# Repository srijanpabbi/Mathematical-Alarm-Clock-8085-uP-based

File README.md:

# Mathematical-Alarm-Clock
#[Find PDF in git repo(Brief Document)]
This device aims to make turning off an alarm a slightly more involving task, forcing the user to focus on the device for some time hence breaking the sleep. It will keep track of time using a RTC and will sound an alarm on the preset time and throw a randomly generated integer based mathematical problem at the user(+,-,/,*), the alarm will stop ringing as soon as the user enters the correct answer to the question. This projects will incorporate a display, a keypad, alarm sounding system(buzzer), and a RTC.

## NETAJI SUBHAS INSTITUTE OFTECHNOLOGY

## DIVISION OFELECTRONICS AND COMMUNICATIONENGINEERING

### EC316 MICROPROCESSORLABPROJECTREPORT

# Mathematical Alarm Clock

## ANINTEL8085 MICROPROCESSOR BASED PROJECT

### Submitted by

### Prabhat Gupta (124EC15)

### Srijan Pabbi (173EC15)

### Submitted to

### Prof. Dhananjay V. Gadre

### May, 2018

## Contents

- 1 Abstract
- 2 Background And Motivation
- 3 Justification
- 4 Block Diagram
- 5 Technical Details
   - 5.1 Hardware
      - 5.1.1 Core Microprocessor (Intel 80C85)
      - 5.1.2 Peripherals And Addressing
      - 5.1.3 RTC(Real Time Clock)
      - 5.1.4 20x4 Character LCD
      - 5.1.5 Key-Pad
      - 5.1.6 Buzzer
   - 5.2 Software Implementation and Interesting Concepts
      - 5.2.1 Big Font and LCD Posting Techniques
      - 5.2.2 Key-Pad Scanning
      - 5.2.3 LFSR(Linear Feedback Shift Register) Implementation
      - 5.2.4 User Setup Inputs With Interrupts
      - 5.2.5 Arithmetic Random Problem Generation With Result Check
- 6 Supporting Materials
   - 6.1 Support Links and References
   - 6.2 Project Schematic And Boards
   - 6.3 Bill of Materials

## 1 Abstract

Everyone must have seen the ordinary alarm clocks that sound only when it is set to be alarmed.Why not
to make a normal alarm period an interesting task. It’s time to get rid of the conventional alarm clocks.
Here what comes the mathematical alarm clock. The mathematical alarm clock is a device that modifies
a conventional alarm clock to a more advanced version that not only alarms but it also makes sure that
the user gets out of sleep for solving some mathematical problems.This device aims to make turning on an
alarm a slightly more involving task. It keeps the trackof time and displays it on the lcd. It does so by using
an RTC (parallel data bus). The Alarm can be set using a keypad. At the time of alarm, a buzzer sounds. The
buzzing of the alarm continues as long as the user would not give the correct answers of certain number of
mathematical problems. At the alarm preset time, the device throws a randomly generated integer based
mathematical problem based on simple arithmetic (+). The alarm stops only after the correct answer is
given by the user. The project incorporates a display (LCD 20x4),keypad, buzzer as an alarming system,
parallel bus RTC

## 2 Background And Motivation

EC-311/316 has provided us an opportunity to build this project under the able guidance of Prof Dhanan-
jay Gadre. The idea of this project is to learn and portray the skill of designing a microprocessor based
system and putting whatever we learn in this course into a useful application. This device aims to make
turning on an alarm a slightly more involving task, forcing the user to focus on the device for some time
hence successfully breaking the sleep as compared to normal alarm clocks. Making this project will involve
almost all the steps required for making a embedded system product namely; planning, designing, getting
the pcb fabricated, coding, and a making an enclosure for the final display, and most importantly docu-
menting throughout the process of making it, which will give us experience on how to design a embedded
product from zero to finish.

## 3 Justification

Mathematical Alarm Clock involves the use of a RTC(Real Time Clock) for time keeping, 20x4 character
LCD for display of time and the generated math questions, and a user input keypad, these devices cannot
be used with simple digital logic devices to perform the job we want out of this project. This project must
be able to display time and, perform background mathematical calculations , accept and compare user
inputs to the answers of the questions which it generated randomly. The need to do all this for successful
working of the project the use of a microprocessor which is fairly fast and can perform slightly complex
mathematical calculations is justified.

## 4 Block Diagram

```
Figure 1: Block Diagram of Mathematical Alarm Clock
```

## 5 Technical Details

##### „„„„„„„„„„„„„„„„„„„„„„„„„„„„

### 5.1 Hardware

#### 5.1.1 Core Microprocessor (Intel 80C85)

At the heart of this project is an Intel 80C85 microprocessor( _μ_ P) from OKI Semiconductors is a CMOS im-
plementation of the original TTL 8085 which has a quiescent current of as low as 10mA. The microprocessor
has a 64KB memory address space and 256 bytes of I/O space. In this case the 8085 is running at 3MHz
from the clock of a 6MHz crystal oscillator.

```
Figure 2: OKI 8085
```

#### 5.1.2 Peripherals And Addressing

This project employs a Atmel ROM 28C256, Intel 8155 PPI+RAM+Timer, Maxim DS12887 RTC, as periph-
erals for the microprocessor and hence they occupy some part of the 8085’s address space.

- Atmel ROM 28C256: Is a 32KB rom which is over kill for this project but was chosen due to its ready
    availability and most of the address space of the 8085 microprocessor is not in use.
    -The address space for the ROM ranges from 0000hto 0FFFh.
    -Chip Select(CS) for this IC is connected toA 15 of the _μ_ P
- Intel 8155: Is a IC specially developed to be used with the Intel 8085 _μ_ P. It has 256bytes of RAM, 3
    I/O ports 2 of 8bit and 1 of 6bit, with handshake capability using the former as I/O and the latter for
    handshaking, and a 8 bit timer with clock out.
    -The address space for the RAM ranges from 8000hto 80FFh.
    -The IO addresses for 8155CWR-00h, PORTA-01h, PORTB-02h, PORTC-03h
    -Chip Select(CS) for this IC is connected toA 15 of the _μ_ P
- RTC: This IC is a complete package of an RTC, battery, and crystal, along with a non-volatile RAM in
    the RTC. This chip implements the Intel Bus Protocol Internally and hence can be memory mapped.
    -The address space for the RTC ranges from 8100hto 8180h.
    -Chip Select(CS) for this IC is connected via a decoding logic as shown in Figure 7

#### 5.1.3 RTC(Real Time Clock)

The real time clock employed for this project DS12887A from Maxim Integrated is a parallel bus RTC with
data exchange via the Intel bus protocol implemented internally. This RTC comes in a 24 pin EDIP package
with internally implemented crystal oscillator and a battery. It can count time on both binary as well as
BCD format with one-time of the day alarm, and an added feature of daylight saving by keeping track
of the exact day,date,year,and century of the millennium. Alongside the basic time keeping features, it
can interrupt the processor about an alarm situation. It can also produce a square wave out of various
frequencies which can be used to drive an alarm sounding system.
The following is the schematic implementation of the RTC.

#### 5.1.4 20x4 Character LCD

The display used in our project is 20X4 LCD display. It is said so as it has 4 rows with 20 characters each.
It uses HD44780 driver. The customized characters are generated using CGRAM. 7 special characters are
stored at seven locations of CGRAM. Using these seven characters any of the character or digit can be
produced. Its contrast and brightness are controlled using two independent presets.

#### 5.1.5 Key-Pad

The keypad used is 4X3 that means it has 4 rows and 3 columns. The switches that are used in the keypad
matrix is 40XX tactile switches. It is interfaced using polling technique. In the polling technique, each
switch press is detected by polling individual switches. In this, rows are treated as input and columns as
output. A switch is identified by outputting through columns and inputting through rows.

#### 5.1.6 Buzzer

The buzzer used here is the D.C. buzzer. It is derived through a port pin of 8155 using a transistor as a
switch.

### 5.2 Software Implementation and Interesting Concepts

#### 5.2.1 Big Font and LCD Posting Techniques

Big Font or customized characters are generated using the CGRAM of the lcd. For generating these char-
acters, some special patterns(7) are stored in the CGRAM. Using these seven patterns, by appropriate
positioning, any big character can be generated.

```
(a) Decimal Digits In Bigfont
```

```
(b) Building Blocks For The Digits
```

```
In order to initialize the LCD the following set of commands need to be sent on the LCD port using
the command function explained later. The first command is used to set the LCD into the 8 bit
data acceptance mode along with a 2 line spill over, which means that if the first line is filled with
characters, the next character sent will be automatically printed in the next line. The second command
clears the LCD of any previous garbage value. Next comes the display on command and the cursor
mode determination. At the end the entry mode is specifier which determines the movement of data
or the cursor on the data input to the LCD.

1 LCD_INIT : MVI C, 38h ; 8 bit 2 line mode
2 CALL SEND_CMD
3 MVI C, 0 1 h          ; clear lcd
4 CALL SEND_CMD
5 MVI C , 0 Ch          ; display on, cursoroff, blinkoff
6 CALL SEND_CMD
7 MVI C, 0 6 h          ; entry mode
8 CALL SEND_CMD
9 RET
```

- The following are two subroutines which are used to send either data or commands to the LCD
    display. Both of them follow a strict protocol in which first the data or command word is made
    available on the PORTB lines of the 8155. The protocol next requires the LCDRS to be either high or
    low depending on the type of word, data or command. Next a pulse of LCDEN is required for the
    LCD controller to take in the data after which a delay is given to perform the operation successfully
    without any interference.
1 SEND_DATA : PUSH PSW ; C f o r a r g
2 MOV A, C ;DATA OUT
3 OUT PORTB
4 IN PORTA

5 ORI LCDRS ; f o r making r s 1
6 OUT PORTA ; s e n d i n g r s b e f o r e l c d _ e n
7 ORI LCDEN ; EN p u l s e
8 OUT PORTA
9 ANI 0FBh
10 OUT PORTA
11 CALL DELAY_2MS
12 POP PSW
13 RET
14
15 SEND_CMD : PUSH PSW ; C f o r a r g
16 MOV A, C ;COMMAND OUT
17 OUT PORTB
18 IN PORTA
19 ANI 0FDh ; f o r making r s 0
20 OUT PORTA ; s e n d i n g r s b e f o r e l c d _ e n
21 ORI LCDEN ; EN p u l s e
22 OUT PORTA
23 ANI 0FBh
24 OUT PORTA
25 CALL DELAY_2MS
26 POP PSW
27 RET
28

#### 5.2.2 Key-Pad Scanning

```
Figure 4: Connections To port A and C
```
```
It is interfaced using polling technique. In the polling tech-
nique, each switch press is detected by polling individual
switches. In this, rows are treated as input and columns
as output. A switch is identified by outputting through
columns and inputting through rows.
```
1
2 KEYPAD : PUSH PSW
3 PUSH H
4 COL1 : IN PORTA ; i n p u t c u r r e n t s t a t e o f portA
5 ANI 0 F7h ; make t h e K_5 b i t a s 0 t o r e a d i n p u t s f o r c o l 1 o n l y
6 OUT PORTA
7 CALL DELAY_2MS ; debouncing d e l a y
8 IN PORTC ; r e a d t h e column
9 ANI 0Fh
10 PRES1 : CPI 0Eh ; i s b u t t o n i n row 1 p r e s s e d?
11 JNZ PRES
12 MVI A, 0 1 h
13 JMP ENDKEYPAD
14 PRES4 : CPI 0Dh ; i s b u t t o n i n row 2 p r e s s e d?
15 JNZ PRES
16 MVI A, 0 4 h
17 JMP ENDKEYPAD
18 PRES7 : CPI 0Bh ; i s b u t t o n i n row 3 p r e s s e d?
19 JNZ PRESS
20 MVI A, 0 7 h
21 JMP ENDKEYPAD
22 PRESS10 : CPI 07 h ; i s b u t t o n i n row 4 p r e s s e d?
23 JNZ COL
24 MVI A, 0 Ah
25 JMP ENDKEYPAD
26
27 COL2 :...
28
29 COL3 :...
30
31 ENDKEYPAD :
32 CPI 0Fh ; i s no b u t t o n p r e s s e d?
33 JZ COL1 ; i f t h a t i s t h e c a s e t h e n c o n t i n u e p o l l i n g
34 LXI H, PRESSED
35 MOV M, A ; s t o r e t h e p r e s s e d
36 CALL DELAY_500MS
37 IN PORTA
38 ORI 38 h make t h e K_5 , 6 , 7 i n a c t i v e
39 OUT PORTA
40 POP H
41 POP PSW
42 RET
43

Figure 5: Keypad Scanning Algorithm Flowchart

#### 5.2.3 LFSR(Linear Feedback Shift Register) Implementation

```
Figure 6: Flowchart of LFSR Algorithm
```
```
It is an algorithm to generate random numbers. In this
method we have two components- seed and mask. Algo-
rithm goes this way: seed value is masked using mask value
such that the bits in seed, corresponding to the ones in mask
value, are XORed and the resultant is moved to the MSB of
seed and the other bits are shifted one to left. In this way we
generate a random number each time this cycle is repeated.
1 LFSR : PUSH PSW ; RET VAL IN THE SEED LOC
2 PUSH B
3 PUSH D
4 PUSH H
5 LXI H, SEED
6 MOV A,M ; r e t r i e v e s e e d
7 LXI H, BITS
8 ANA M ; r e t r i e v e mask b i t s
9 MVI B , 0 0H ; c o u n t
10 MVI C, 0 8H ; 8 b i t s
11 LOOP1 : RRC ; LSB i n CARRY
12 JNC NXT
13 INR B ; i n c r e m e n t B i s c a r r y i s 1
14 NXT1 : DCR C
15 JNZ LOOP
16 MOV A, B
17 RLC
18 RLC
19 RLC
20 RLC
21 RLC
22 RLC
23 RLC
24 ANI 80H
25 MOV B , A ; s t o r e t h e XOR r e s u l t
26 ; i n t h e MSB o f B
27 LXI H, SEED
28 MOV A,M
29 STC
30 CMC
31 RAR ; r o t a t e SEED making MSB=
32 ORA B ; put t h e new MSB v a l from B
33 STA SEED ; r e p l a c e o l d s e e d
34 ; v a l with new rand no.
35 POP H
36 POP D
37 POP B
38 POP PSW
39 RET
```

#### 5.2.4 User Setup Inputs With Interrupts

Interrupt RST7.5 is used as an user interface to update the timings of normal day time and the alarm time.
It’s a user interacting switch which is connected to RST7.5. Each time this switch is pressed, program
transfers to settings window to set either day time or alarm time. According to the option selected, settings
transfer to set the required time.

#### 5.2.5 Arithmetic Random Problem Generation With Result Check

Each time alarm time matches the regular time, program transfers to a section in which some random
problems(based on addition) are generated using LFSR algorithm. The result to these problems are also
calculated and stored n the memory at the same time. The results are checked against the ones that are
inputted by the user. Only when the result matches the input the alarm goes off otherwise more random
problems are generated.

## 6 Supporting Materials

##### „„„„„„„„„„„„„„„„„„„„„„„„„„„„

### 6.1 Support Links and References

- Youtube Video: https://www.youtube.com/watch?v=FnkgJ6MPxQ
- GITHUB Link for Code: https://github.com/srijanpabbi/Mathematical-Alarm-Clock-8085-uP-based
- Programmer and Assembler related Material: https://drive.google.com/drive/folders/0B3dkOo5f1Sb-
    ZHQ5bHRYb3ZnR2c?usp=sharing
- Other 8085 Projects for Reference: [http://www.8085projects.in/](http://www.8085projects.in/)
- A forum discussion on LCD bigfont: https://www.avrfreaks.net/forum/alphanumeric-lcd-hd44780-
    big-font-big-digits-generator-excel-sheet
- Full End to End character LCD tutorial in C as well as Assembly Language
- RTC Datasheet: https://pdfserv.maximintegrated.com/en/ds/DS12885-DS12C887A.pdf
- OKI 80C85 Datasheet: [http://elearning.tukenya.ac.ke/course/view.php?id=](http://elearning.tukenya.ac.ke/course/view.php?id=)
- LCD Controller Datasheet: https://www.sparkfun.com/datasheets/LCD/HD44780.pdf

### 6.2 Project Schematic And Boards

```
Figure 7: Logic Board Schematic
```

```
Figure 8: Logic Board Layout
```
Figure 9: User Interface Board Schematic

```
Figure 10: User Interface Board Layout
```
### 6.3 Bill of Materials

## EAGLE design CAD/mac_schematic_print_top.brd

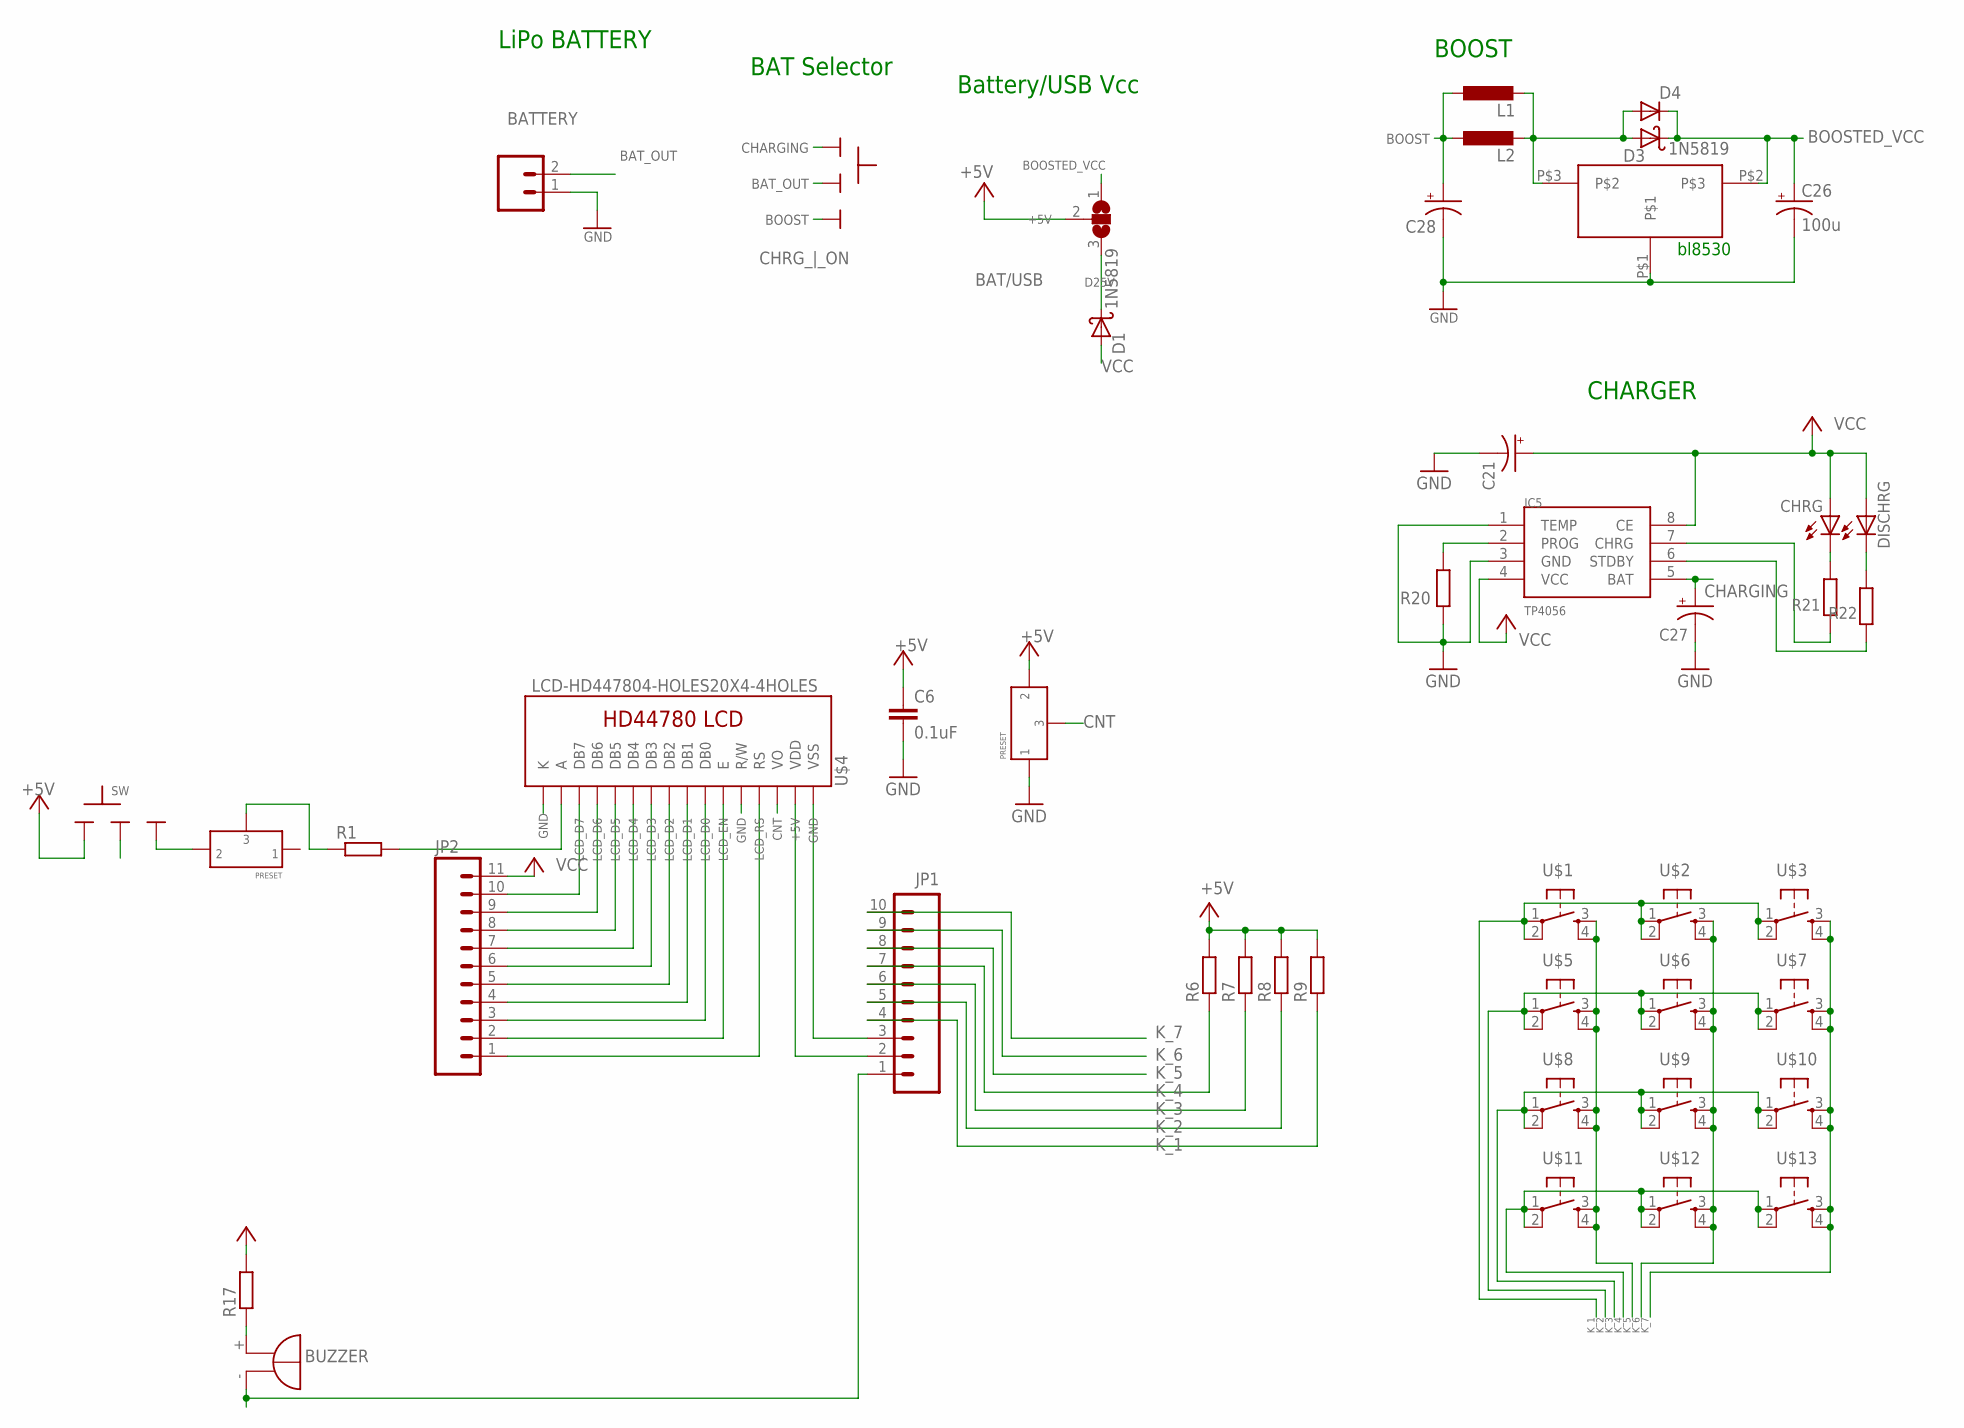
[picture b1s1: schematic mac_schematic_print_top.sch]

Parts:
BAT/USB: SJ2W; SJ_2
BATTERY: M02JST-PTH-2; 02P
C6: 0.1uF; C0805K
C21, C27, C28: 10u; C/6032-28R
C26: 100u; C/6032-28R
CHRG: LED3MM
CHRG_|_ON: SLIDESWITCH-BIG; BIGSWITCH
D1, D3: 1N5819; DO41-10
D4: DIODE_DIODE-DO214AC; DIODE_DO214AC
DISCHRG: LED3MM
IC5: TP4056; SOP-8
IC6: BL8530_5V
JP1: M10SILK_FEMALE_PTH; 1X10
JP2: M11PTH; 1X11
L1: L-EU6000-XXX-RC; 6000-XXXX-RC
L2: 47uH; L5650M
PRESET, PRESET1: PRESET; PRESET_LR
R1, R6, R7, R8, R9, R17, R20: R-EU_0204/7; 0204/7
R21, R22: 470; 0204/7
SG1: BUZZER; F/TMB
SW: SLIDESWITCH-BIG; BIGSWITCH
U$1, U$2, U$3, U$5, U$6, U$7, U$8, U$9, U$10, U$11, U$12, U$13: OMRON_SWITCH_40-XX; B3F-40XX
U$4: LCD-HD447804-HOLES20X4-4HOLES; LCD-20X4-4HOLES

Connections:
+5V: BAT/USB.2, C6.1, JP1.2, PRESET.P$2 (2), R6.2, R7.2, R8.2, R9.2, R17.2, SW.1, U$4.P$2 (VDD)
BAT_OUT: BATTERY.2, CHRG_|_ON.2
BOOST: C28.+, CHRG_|_ON.3, L1.1, L2.1
BOOSTED_VCC: BAT/USB.1, C26.+, D3.C, D4.C, IC6.P$2
CHARGING: C27.+, CHRG_|_ON.1, IC5.5 (BAT)
CNT: PRESET.P$3 (3), U$4.P$3 (VO)
D25V: BAT/USB.3, D1.C
GND: BATTERY.1, C6.2, C21.-, C26.-, C27.-, C28.-, IC5.1 (TEMP), IC5.3 (GND), IC6.P$1, JP1.3, PRESET.P$1 (1), R20.1, U$4.P$1 (VSS), U$4.P$5 (R/W), U$4.P$16 (K)
K_1: JP1.4, R9.1, U$1.1, U$1.2 (P1), U$2.1, U$2.2 (P1), U$3.1, U$3.2 (P1)
K_2: JP1.5, R8.1, U$5.1, U$5.2 (P1), U$6.1, U$6.2 (P1), U$7.1, U$7.2 (P1)
K_3: JP1.6, R7.1, U$8.1, U$8.2 (P1), U$9.1, U$9.2 (P1), U$10.1, U$10.2 (P1)
K_4: JP1.7, R6.1, U$11.1, U$11.2 (P1), U$12.1, U$12.2 (P1), U$13.1, U$13.2 (P1)
K_5: JP1.8, U$1.3 (S), U$1.4 (S1), U$5.3 (S), U$5.4 (S1), U$8.3 (S), U$8.4 (S1), U$11.3 (S), U$11.4 (S1)
K_6: JP1.9, U$2.3 (S), U$2.4 (S1), U$6.3 (S), U$6.4 (S1), U$9.3 (S), U$9.4 (S1), U$12.3 (S), U$12.4 (S1)
K_7: JP1.10, U$3.3 (S), U$3.4 (S1), U$7.3 (S), U$7.4 (S1), U$10.3 (S), U$10.4 (S1), U$13.3 (S), U$13.4 (S1)
LCD_D0: JP2.3, U$4.P$7 (DB0)
LCD_D1: JP2.4, U$4.P$8 (DB1)
LCD_D2: JP2.5, U$4.P$9 (DB2)
LCD_D3: JP2.6, U$4.P$10 (DB3)
LCD_D4: JP2.7, U$4.P$11 (DB4)
LCD_D5: JP2.8, U$4.P$12 (DB5)
LCD_D6: JP2.9, U$4.P$13 (DB6)
LCD_D7: JP2.10, U$4.P$14 (DB7)
LCD_EN: JP2.2, U$4.P$6 (E)
LCD_RS: JP2.1, U$4.P$4 (RS)
unnamed: JP1.1, SG1.-
unnamed: PRESET1.P$2 (2), SW.3
unnamed: R1.2, U$4.P$15 (A)
unnamed: PRESET1.P$3 (3), R1.1
unnamed: R17.1, SG1.+
unnamed: IC5.2 (PROG), R20.2
unnamed: IC5.7 (CHRG), R21.1
unnamed: IC5.6 (STDBY), R22.1
unnamed: CHRG.K (C), R21.2
unnamed: DISCHRG.K (C), R22.2
unnamed: D3.A, D4.A, IC6.P$3, L1.2, L2.2
VCC: C21.+, CHRG.A, D1.A, DISCHRG.A, IC5.4 (VCC), IC5.8 (CE), JP2.11

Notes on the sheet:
CHARGER
BOOST
bl8530
LiPo BATTERY
BAT Selector
Battery/USB Vcc

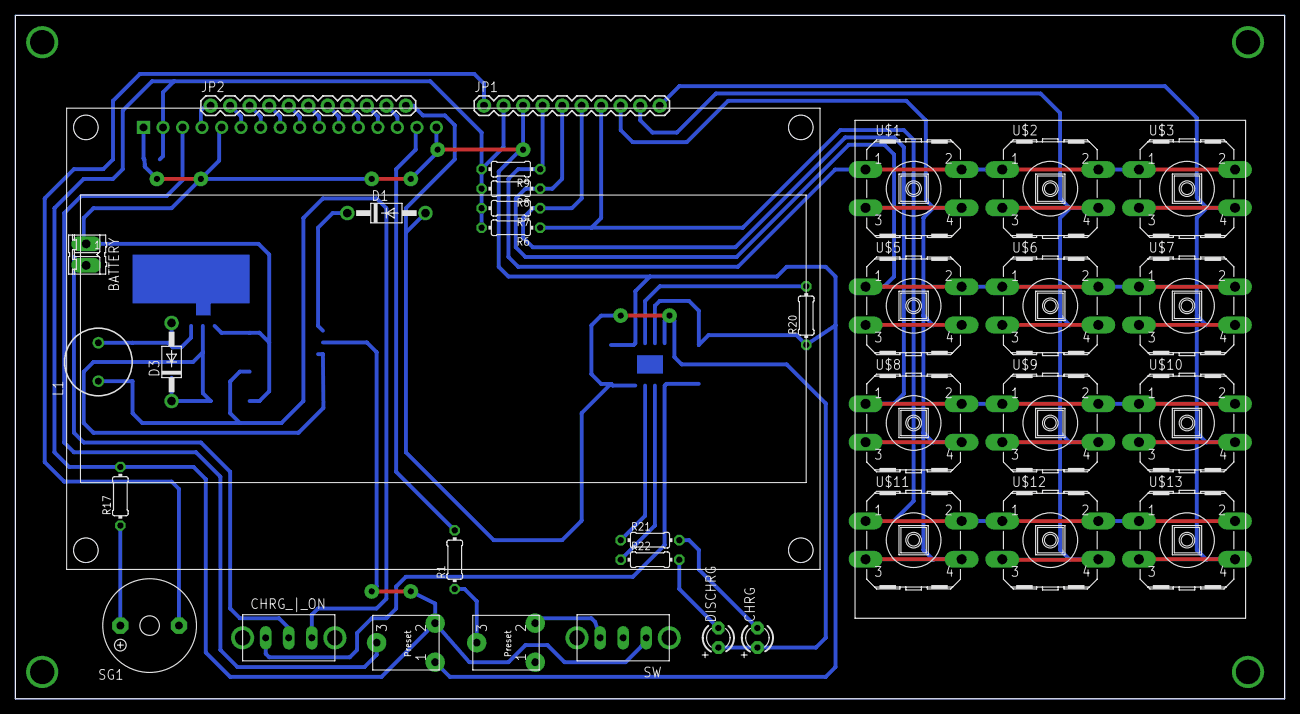
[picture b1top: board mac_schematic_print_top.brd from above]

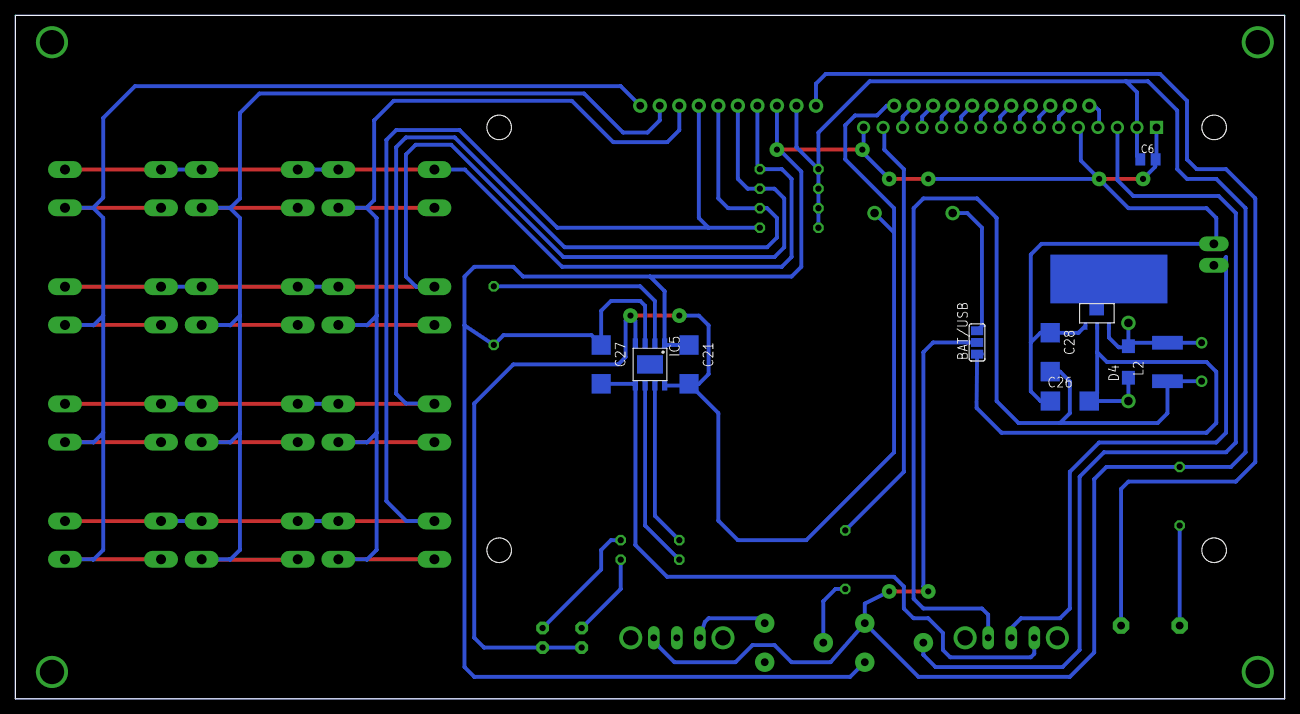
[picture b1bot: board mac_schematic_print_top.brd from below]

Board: 2 copper layers, 165.1 x 88.9 mm, 45 parts (10 on the bottom side), 37 nets.

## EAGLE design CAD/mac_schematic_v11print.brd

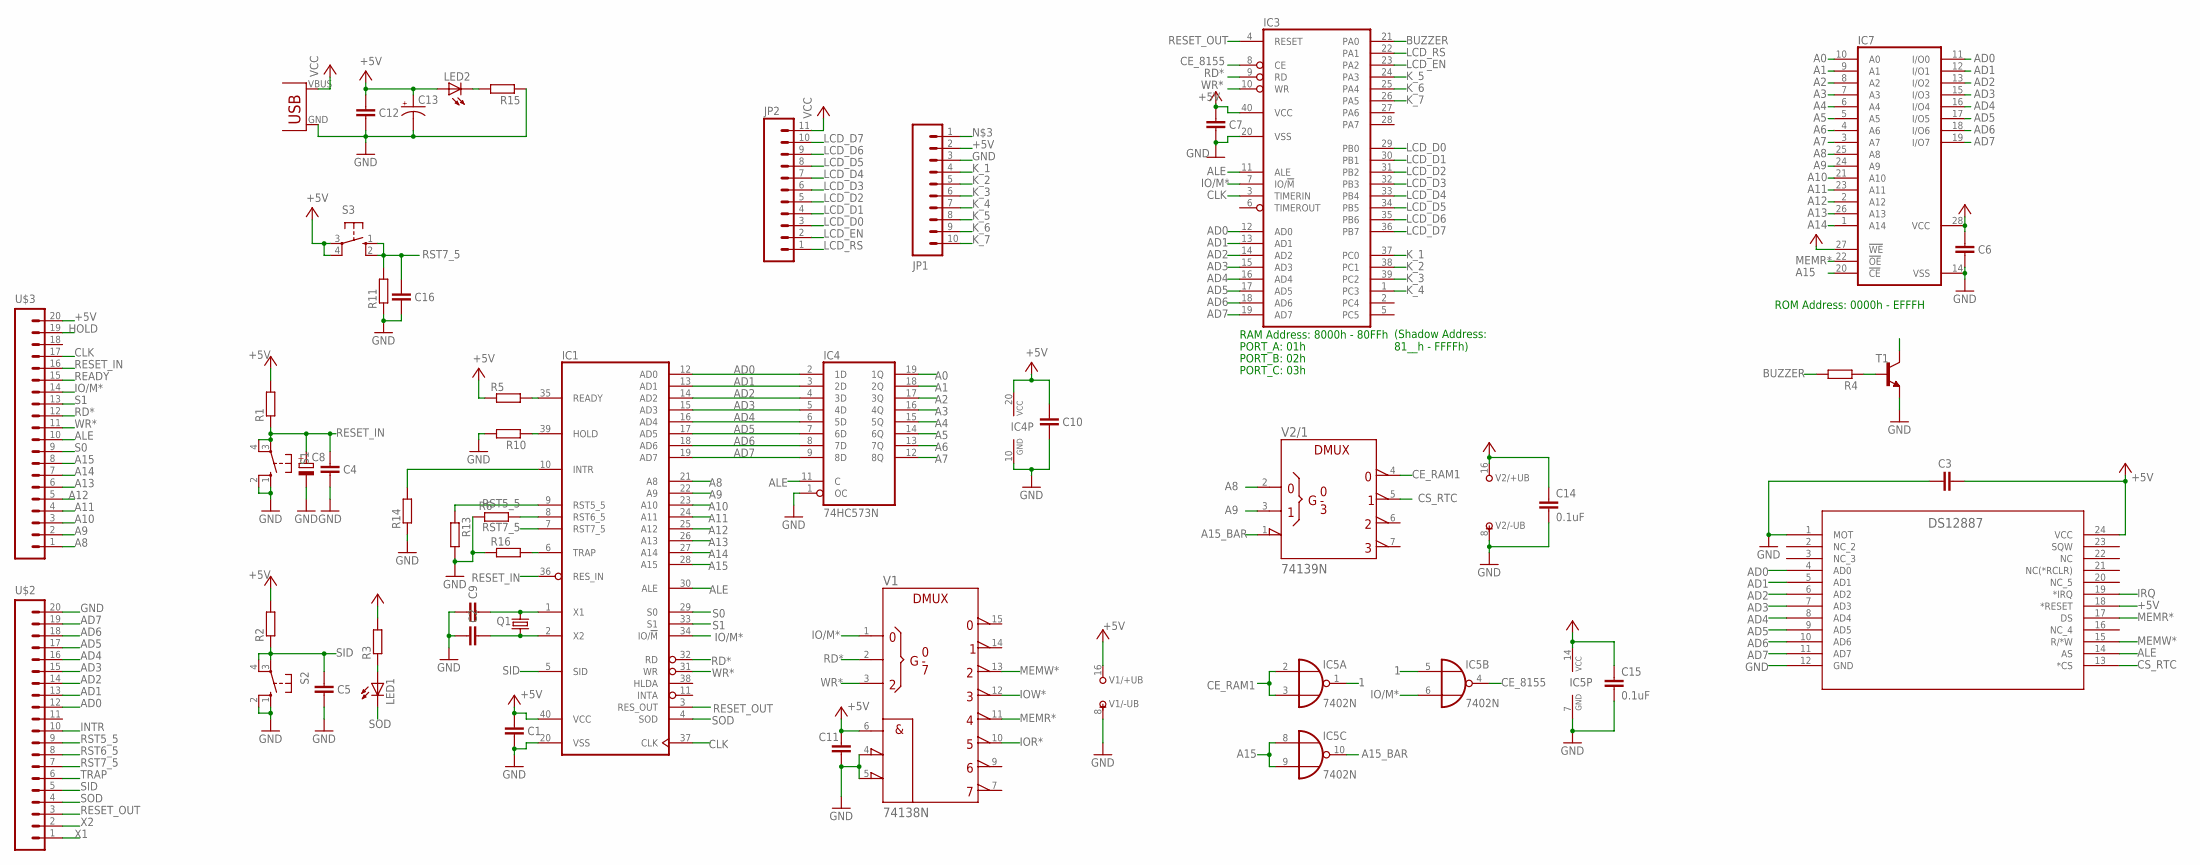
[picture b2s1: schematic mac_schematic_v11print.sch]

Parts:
C1, C2, C3, C4, C5, C6, C7, C9, C10, C11, C12, C16: C-EUC0805K; C0805K
C8: CPOL-EUE2.5-5; E2,5-5
C13: CAP_POL_10V; C/6032-28R
C14, C15: 0.1uF; C0805K
IC1: 8085; DIL40
IC3: 8155; DIL40
IC4: 74HC573N; DIL20
IC5: 7402N; DIL14
IC7: 58C256P; DIL28-6
JP1: M10SILK_FEMALE_PTH; 1X10
JP2: M11PTH; 1X11
LED1, LED2: LED3MM
Q1: CRYSTALHC49U-V; HC49U-V
R1, R2, R3, R4, R5, R6, R10, R11, R13, R14, R15, R16: R-EU_0204/7; 0204/7
S1, S2, S3: 40-XX; B3F-40XX
T1: BC547-NPN-TO92-CBE; TO92-CBE
U1: DS12887; 21-0241A_24
U$1: USB(POWER)
U$2, U$3: M20; LONDPAD
V1: 74138N; DIL16
V2: 74139N; DIL16

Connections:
1: IC5.1 (O), IC5.5 (I0)
+5V: C1.1, C3.2, C6.1, C7.1, C10.1, C11.1, C12.1, C13.+, C14.1, C15.1, IC1.40 (VCC), IC3.40 (VCC), IC4.20 (VCC), IC5.14 (VCC), IC7.27 (!WE), IC7.28 (VCC), JP1.2, LED2.A, R1.2, R2.2, R3.2, R5.1, S3.3, S3.4 (P1), U1.18 (*RESET), U1.24 (VCC), U$3.20, V1.6 (G1), V1.16 (+UB), V2.16 (+UB)
A0: IC4.19 (1Q), IC7.10 (A0)
A1: IC4.18 (2Q), IC7.9 (A1)
A2: IC4.17 (3Q), IC7.8 (A2)
A3: IC4.16 (4Q), IC7.7 (A3)
A4: IC4.15 (5Q), IC7.6 (A4)
A5: IC4.14 (6Q), IC7.5 (A5)
A6: IC4.13 (7Q), IC7.4 (A6)
A7: IC4.12 (8Q), IC7.3 (A7)
A8: IC1.21 (A8), IC7.25 (A8), U$3.1, V2.2 (A)
A9: IC1.22 (A9), IC7.24 (A9), U$3.2, V2.3 (B)
A10: IC1.23 (A10), IC7.21 (A10), U$3.3
A11: IC1.24 (A11), IC7.23 (A11), U$3.4
A12: IC1.25 (A12), IC7.2 (A12), U$3.5
A13: IC1.26 (A13), IC7.26 (A13), U$3.6
A14: IC1.27 (A14), IC7.1 (A14), U$3.7
A15: IC1.28 (A15), IC5.8 (I0), IC5.9 (I1), IC7.20 (!CE), U$3.8
A15_BAR: IC5.10 (O), V2.1 (!G)
AD0: IC1.12 (AD0), IC3.12 (AD0), IC4.2 (1D), IC7.11 (I/O0), U1.4 (AD0), U$2.12
AD1: IC1.13 (AD1), IC3.13 (AD1), IC4.3 (2D), IC7.12 (I/O1), U1.5 (AD1), U$2.13
AD2: IC1.14 (AD2), IC3.14 (AD2), IC4.4 (3D), IC7.13 (I/O2), U1.6 (AD2), U$2.14
AD3: IC1.15 (AD3), IC3.15 (AD3), IC4.5 (4D), IC7.15 (I/O3), U1.7 (AD3), U$2.15
AD4: IC1.16 (AD4), IC3.16 (AD4), IC4.6 (5D), IC7.16 (I/O4), U1.8 (AD4), U$2.16
AD5: IC1.17 (AD5), IC3.17 (AD5), IC4.7 (6D), IC7.17 (I/O5), U1.9 (AD5), U$2.17
AD6: IC1.18 (AD6), IC3.18 (AD6), IC4.8 (7D), IC7.18 (I/O6), U1.10 (AD6), U$2.18
AD7: IC1.19 (AD7), IC3.19 (AD7), IC4.9 (8D), IC7.19 (I/O7), U1.11 (AD7), U$2.19
ALE: IC1.30 (ALE), IC3.11 (ALE), IC4.11 (C), U1.14 (AS), U$3.10
BUZZER: IC3.21 (PA0), R4.2
CE_8155: IC3.8 (CE), IC5.4 (O)
CE_RAM1: IC5.2 (I0), IC5.3 (I1), V2.4 (Y0)
CLK: IC1.37 (CLK), IC3.3 (TIMERIN), U$3.17
CS_RTC: U1.13 (*CS), V2.5 (Y1)
GND: C1.2, C2.1, C3.1, C4.2, C5.2, C6.2, C7.2, C8.-, C9.1, C10.2, C11.2, C12.2, C13.-, C14.2, C15.2, C16.2, IC1.20 (VSS), IC3.20 (VSS), IC4.1 (OC), IC4.10 (GND), IC5.7 (GND), IC7.14 (VSS), JP1.3, R6.1, R10.2, R11.1, R13.2, R14.1, R15.1, R16.1, S1.1 (S), S1.2 (S1), S2.1 (S), S2.2 (S1), T1.E, U1.1 (MOT), U1.12 (GND), U$1.GND, U$2.20, V1.4 (!G2A), V1.5 (!G2B), V1.8 (-UB), V2.8 (-UB)
HOLD: IC1.39 (HOLD), R10.1, U$3.19
INTR: IC1.10 (INTR), R14.2, U$2.10
IO/M*: IC1.34 (IO/!M), IC3.7 (IO/!M), IC5.6 (I1), U$3.14, V1.1 (A)
IOR*: V1.10 (Y5)
IOW*: V1.12 (Y3)
IRQ: U1.19 (*IRQ)
K_1: IC3.37 (PC0), JP1.4
K_2: IC3.38 (PC1), JP1.5
K_3: IC3.39 (PC2), JP1.6
K_4: IC3.1 (PC3), JP1.7
K_5: IC3.24 (PA3), JP1.8
K_6: IC3.25 (PA4), JP1.9
K_7: IC3.26 (PA5), JP1.10
LCD_D0: IC3.29 (PB0), JP2.3
LCD_D1: IC3.30 (PB1), JP2.4
LCD_D2: IC3.31 (PB2), JP2.5
LCD_D3: IC3.32 (PB3), JP2.6
LCD_D4: IC3.33 (PB4), JP2.7
LCD_D5: IC3.34 (PB5), JP2.8
LCD_D6: IC3.35 (PB6), JP2.9
LCD_D7: IC3.36 (PB7), JP2.10
LCD_EN: IC3.23 (PA2), JP2.2
LCD_RS: IC3.22 (PA1), JP2.1
MEMR*: IC7.22 (!OE), U1.17 (DS), V1.11 (Y4)
MEMW*: U1.15 (R/*W), V1.13 (Y2)
unnamed: LED1.A, R3.1
unnamed: JP1.1, T1.C
unnamed: R4.1, T1.B
unnamed: LED2.K (C), R15.2
RD*: IC1.32 (RD), IC3.9 (RD), U$3.12, V1.2 (B)
READY: IC1.35 (READY), R5.2, U$3.15
RESET_IN: C4.1, C8.+, IC1.36 (RES_IN), R1.1, S1.3, S1.4 (P1), U$3.16
RESET_OUT: IC1.3 (RES_OUT), IC3.4 (RESET), U$2.3
RST5_5: IC1.9 (RST5_5), R13.1, U$2.9
RST6_5: IC1.8 (RST6_5), R6.2, U$2.8
RST7_5: C16.1, IC1.7 (RST7_5), R11.2, S3.1 (S), S3.2 (S1), U$2.7
S0: IC1.29 (S0), U$3.9
S1: IC1.33 (S1), U$3.13
SID: C5.1, IC1.5 (SID), R2.1, S2.3, S2.4 (P1), U$2.5
SOD: IC1.4 (SOD), LED1.K (C), U$2.4
TRAP: IC1.6 (TRAP), R16.2, U$2.6
VCC: JP2.11, U$1.VBUS (VCC)
WR*: IC1.31 (WR), IC3.10 (WR), U$3.11, V1.3 (C)
X1: C9.2, IC1.1 (X1), Q1.2, U$2.1
X2: C2.2, IC1.2 (X2), Q1.1, U$2.2

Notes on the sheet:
ROM Address: 0000h - EFFFH
RAM Address: 8000h - 80FFh
PORT_A: 01h
PORT_B: 02h
PORT_C: 03h
(Shadow Address: 81__h - FFFFh)

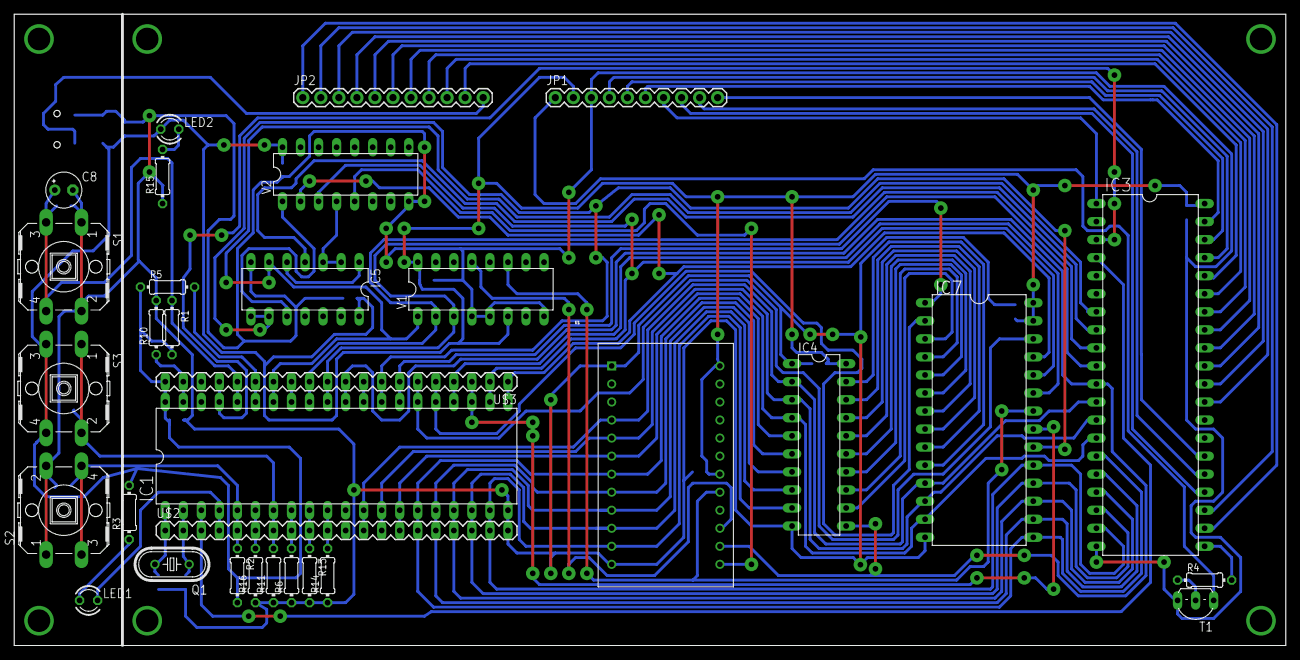
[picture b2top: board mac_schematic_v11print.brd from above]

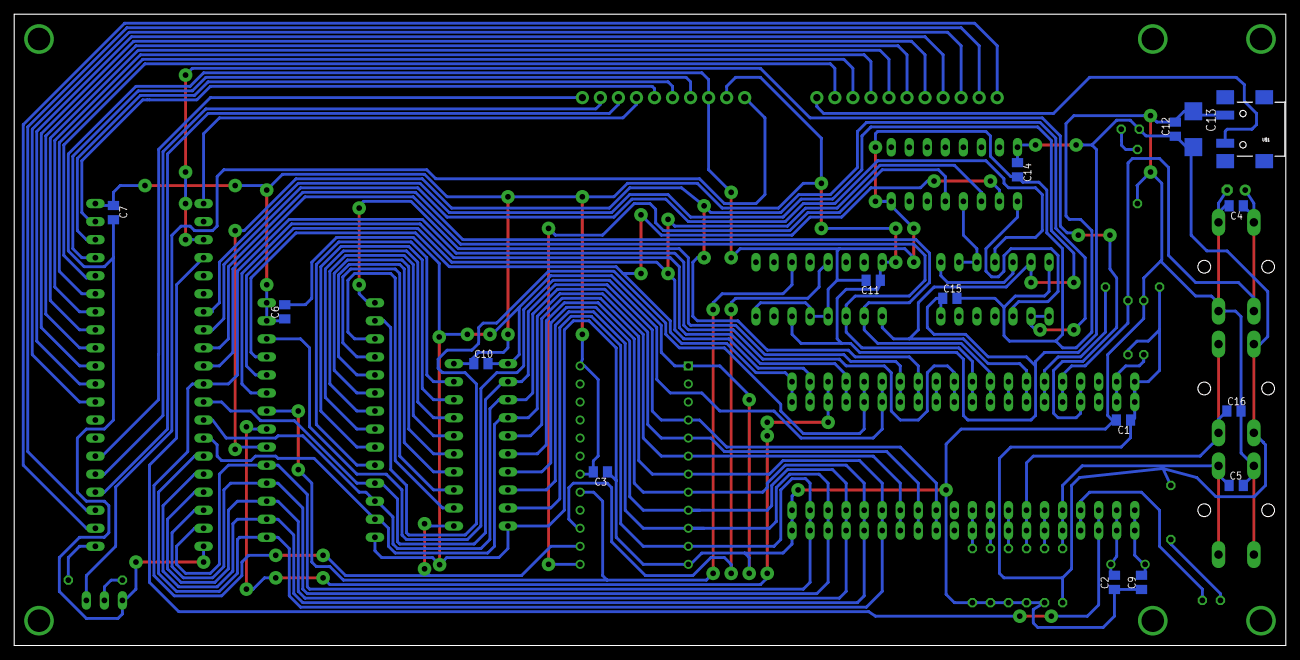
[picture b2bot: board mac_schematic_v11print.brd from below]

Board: 2 copper layers, 179.1 x 88.9 mm, 48 parts (16 on the bottom side), 76 nets.

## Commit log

2018-02-03 Added mathematical_alarm_clock.pdf
2018-02-11 Add files via upload
    RTC_DS12887_MSP430_Interfacing
2019-03-02 Create temp

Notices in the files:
parts and their libraries:
SparkFun-Connectors: Licensing: Creative Commons ShareAlike 4.0 International - https://creativecommons.org/licenses/by-sa/4.0
